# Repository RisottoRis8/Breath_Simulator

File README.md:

# Syringe-Based Breathing Simulator

University biomedical engineering project developed by Gruppo Viola: a motorized syringe generates controlled air flow at its outlet. The system combines a BLDC motor with an ESCON 50/5 drive, encoder feedback, Sensirion pressure or mass-flow sensing, PID control, BLE communication and a desktop monitoring GUI.

This repository presents the final ESP32-based system together with its electronics, control software, measurement data and technical documentation. Earlier firmware, interface and hardware iterations are preserved separately as supporting development history.

## System overview

The final firmware runs on an ESP32 and coordinates:

- flow sensing through SDP810 or SFM3300 devices;
- motor control through the ESCON driver;
- incremental encoder feedback and homing signals;
- PID regulation of the generated flow;
- external SPI EEPROM storage;
- HM-10 compatible BLE telemetry and commands.

The final architecture is supported by a custom control board and a desktop BLE interface. Earlier STM32 and ESP32 bridge implementations are preserved as development iterations.

## Repository map

| Area | Contents |
| --- | --- |
| [docs](docs/) | Report, architecture notes, protocol notes and project catalog |
| [firmware](firmware/) | ESP32 and STM32 firmware area |
| [software/gui](software/gui/) | Main desktop control interface, [main_gui.py](software/gui/main_gui.py) |
| [software/tools](software/tools/) | BLE terminal, CSV visualizer and Python dependency notes |
| [hardware](hardware/) | KiCad boards, custom libraries and board documentation |
| [analysis/matlab](analysis/matlab/) | Measurement interpolation and resistance-analysis scripts |
| [data/measurements/raw](data/measurements/raw/) | Original experimental CSV measurements |
| [mechanical/renders](mechanical/renders/) | Syringe assembly render |
| [archive](archive/) | GUI prototypes and duplicate/legacy experiments |
| [docs/references/datasheets](docs/references/datasheets/) | Component reference documents |
| [archive/sensor-sdp800](archive/sensor-sdp800/) | Sensor sample-code project and documentation |

The detailed working inventory is in [docs/PROJECT_CATALOG.md](docs/PROJECT_CATALOG.md).

## Final system

- **Controller:** [firmware/esp32/main](firmware/esp32/main) coordinates sensing, encoder feedback, motor actuation, PID flow regulation, EEPROM storage and BLE communication.
- **Control interface:** [software/gui/main_gui.py](software/gui/main_gui.py) provides BLE discovery, connection management, real-time flow/position/PWM plots, operating modes, calibration controls, logging and emergency stop.
- **Electronics:** [hardware/motherboard-r2](hardware/motherboard-r2) and [hardware/pogo-adapter](hardware/pogo-adapter) contain the KiCad designs for the control board and sensor adapter. The original motherboard design is preserved as [motherboard-r1](hardware/motherboard-r1).
- **Validation data:** [data/measurements/raw](data/measurements/raw/) contains the experimental acquisitions used during characterization and analysis.

## Communication status

The final ESP32 interface uses an HM-10-compatible BLE service (`FFE0/FFE1`) and telemetry frames in the form `SNSR <flow> <encoder_position> <pwm>`. The communication details are summarized in [docs/protocol.md](docs/protocol.md).

The earlier Nordic UART bridge and STM32 variants remain available in [archive](archive/) as development iterations and are not part of the primary ESP32 control path.

## Running the Python tools

The main GUI requires Python packages including PyQt6, pyqtgraph, bleak and qasync. The BLE terminal declares its dependency in [requirements-ble.txt](software/tools/requirements-ble.txt).

The CSV visualizer is a separate Streamlit utility:

```text
streamlit run software/tools/visualizer.py
```

Its expected columns are `Timestamp_s` and `Pressione_Pa`; the raw measurements commonly use `Time_s` and `Pressure_Pa`, so they are not directly interchangeable yet.

## Firmware and hardware

The Arduino ESP32 sketch is located in [firmware/esp32/main](firmware/esp32/main) and uses the local NimBLE-Arduino library in [firmware/esp32/libraries](firmware/esp32/libraries).

KiCad source files are separated from local state, backups and manufacturing exports. The root [.gitignore](.gitignore) excludes regenerable artifacts while keeping source schematics, PCB files, custom libraries and experimental measurements available for review.

## Project documentation

- [Project catalog](docs/PROJECT_CATALOG.md)
- [Communication protocol notes](docs/protocol.md)
- [Project report](docs/report_biomed.pdf)
- [Code-flow diagram](docs/architecture/code-flow-diagram.drawio)
- [Firmware pseudocode](docs/architecture/codice.pseudo)
- [Assembly render](mechanical/renders/syringe-assembly.jpg)

## Development history

Previous ESP32 sketches, STM32 firmware, BLE bridges and GUI prototypes are preserved in [archive](archive/). They document the iterations that led to the final ESP32 architecture, while the project entrypoints above describe the system delivered by the team.

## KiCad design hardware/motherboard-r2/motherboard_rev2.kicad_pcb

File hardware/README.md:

# Hardware

KiCad source projects, custom libraries and board revisions will be grouped here. Generated manufacturing output and local KiCad state are excluded by the root `.gitignore`.

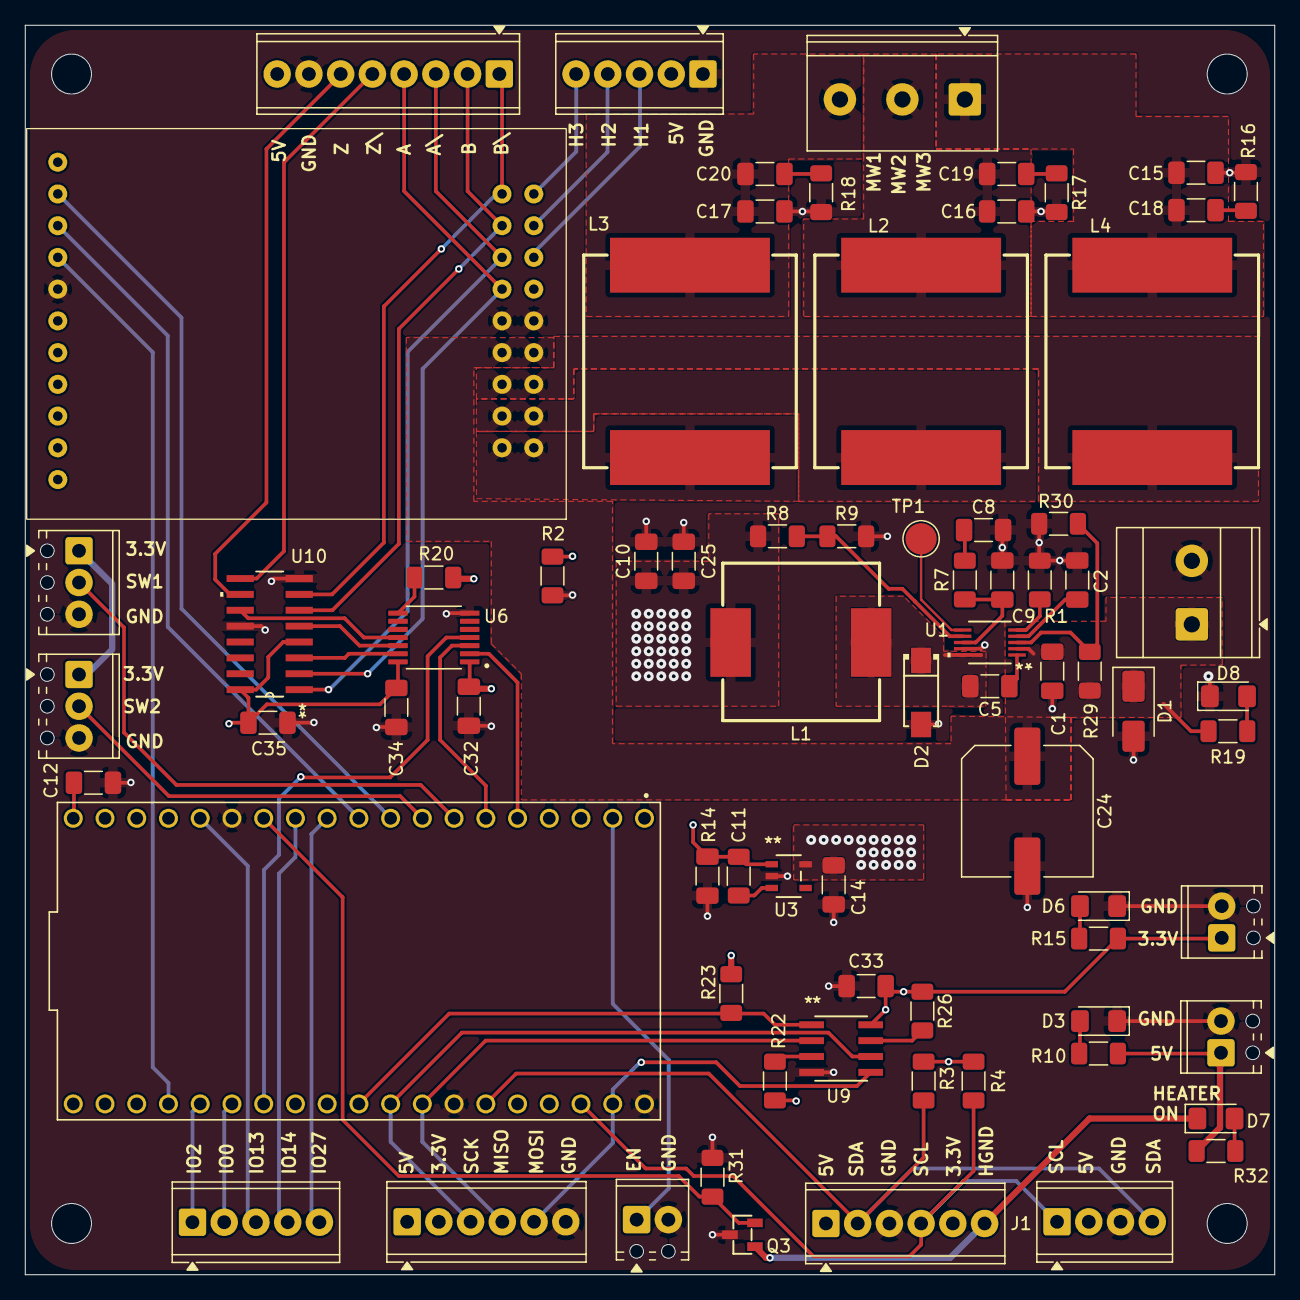
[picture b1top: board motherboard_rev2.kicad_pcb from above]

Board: 4 copper layers, 100.0 x 100.0 mm, 79 parts (0 on the bottom side), 64 nets.

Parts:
C1: 4u7; C_1206_3216Metric_Pad1.33x1.80mm_HandSolder
C2: 6n8; C_1206_3216Metric_Pad1.33x1.80mm_HandSolder
C5, C32, C33, C34, C35: 100n; C_1206_3216Metric_Pad1.33x1.80mm_HandSolder
C8: 1n8; C_1206_3216Metric_Pad1.33x1.80mm_HandSolder
C9: 1p2; C_1206_3216Metric_Pad1.33x1.80mm_HandSolder
C10, C25: 47u; C_1206_3216Metric_Pad1.33x1.80mm_HandSolder
C11, C12, C14: 1u; C_1206_3216Metric_Pad1.33x1.80mm_HandSolder
C15, C16, C17: 150p; C_1206_3216Metric_Pad1.33x1.80mm_HandSolder
C18, C19, C20: 330p; C_1206_3216Metric_Pad1.33x1.80mm_HandSolder
C24: 220u; C_Elec_10x10.2
D1: SMAJ26A; D_SMA
D2: SS24FL; SMA_L4.4-W2.8-LS5.4-RD
D3: LED_ORANGE; LED_1206_3216Metric_Pad1.42x1.75mm_HandSolder
D6: LED_BLUE; LED_1206_3216Metric_Pad1.42x1.75mm_HandSolder
D7: LED_YELLOW; LED_1206_3216Metric_Pad1.42x1.75mm_HandSolder
D8: LED_GREEN; LED_1206_3216Metric_Pad1.42x1.75mm_HandSolder
E1: escon; escon_vero
H1, H2, H3, H4: MountingHole; MountingHole_3.2mm_M3
J1: Conn_01x04; TerminalBlock_Phoenix_MPT-0,5-4-2.54_1x04_P2.54mm_Horizontal
J2, J8: Conn_01x06; TerminalBlock_Phoenix_MPT-0,5-6-2.54_1x06_P2.54mm_Horizontal
J3: Conn_01x08; TerminalBlock_Phoenix_MPT-0,5-8-2.54_1x08_P2.54mm_Horizontal
J5, J6: Conn_01x03; TerminalBlock_Phoenix_MPT-0,5-3-2.54_1x03_P2.54mm_Horizontal
J7, J11: Conn_01x05; TerminalBlock_Phoenix_MPT-0,5-5-2.54_1x05_P2.54mm_Horizontal
J9: Conn_01x02; TerminalBlock_Phoenix_MKDS-3-2-5.08_1x02_P5.08mm_Horizontal
J10: Screw_Terminal_01x03; TerminalBlock_Phoenix_PT-1,5-3-5.0-H_1x03_P5.00mm_Horizontal
J13, J14, J16: Conn_01x02; TerminalBlock_Phoenix_MPT-0,5-2-2.54_1x02_P2.54mm_Horizontal
L1: 47u; IND-SMD_L13.5-W12.6_125CDMCC-DS
L2, L3, L4: 22uH; IND-SMD_L17.0-W17.0_YSPIA1770-100M
Q3: NMOS; SOT-23-3_L2.9-W1.3-P1.90-LS2.4-BR
R1: 249k; R_1206_3216Metric_Pad1.30x1.75mm_HandSolder
R2: 390 ohm; R_1206_3216Metric_Pad1.30x1.75mm_HandSolder
R3, R4: 4.7K; R_1206_3216Metric_Pad1.30x1.75mm_HandSolder
R7: 133k; R_1206_3216Metric_Pad1.30x1.75mm_HandSolder
R8: 52k3; R_1206_3216Metric_Pad1.30x1.75mm_HandSolder
R9, R10, R14, R15, R19, R20, R31: 10k; R_1206_3216Metric_Pad1.30x1.75mm_HandSolder
R16, R17, R18: 390; R_1206_3216Metric_Pad1.30x1.75mm_HandSolder
R22, R23, R26: 10K; R_1206_3216Metric_Pad1.30x1.75mm_HandSolder
R29: 105k; R_1206_3216Metric_Pad1.30x1.75mm_HandSolder
R30: 6k49; R_1206_3216Metric_Pad1.30x1.75mm_HandSolder
R32: 1k; R_1206_3216Metric_Pad1.30x1.75mm_HandSolder
TP1: TestPoint; TestPoint_Pad_D2.5mm
U1: TPS54140ADGQR; DGQ10_1P88X1P57_TEX
U2: NODEMCU-32S; MODULE_NODEMCU-32S
U3: AP2112K-3.3TRG1; SOT_RG1_DIO
U6: TXS0104EPWR; SOP65P640X120-14N
U9: 25LC256-I/SN; SOIC8-N_MC_MCH
U10: AM26LS32ACDR; D16

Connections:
+3.3V: C14.1, C32.1, C33.1, J2.5, J5.1, J6.1, J8.2, J14.1, R3.1, R4.1, R15.1, R20.1, R22.1, R23.1, R26.1, U3.5 (VOUT), U6.1 (VCCA), U9.8 (VCC)
+5V: C10.1, C11.1, C12.1, C25.1, C34.1, C35.1, E1.11 (+5_VDC), J1.2, J2.1, J3.8, J8.1, J11.2, J13.1, L1.2, R2.1, R8.1, R10.1, R14.2, R32.1, U2.J1_19 (5V), U3.1 (VIN), U6.14 (VCCB), U10.4 (G), U10.16 (VCC)
+24V: C1.1, C24.1, D1.1 (A1), E1.7 (Vcc), E1.8 (Vcc), J9.1, R19.1, R29.1, U1.2 (VIN)
/CONNECTORS/ENABLE: J16.1, U2.J1_2 (EN)
/CONNECTORS/ENC_A: E1.12 (ENC_CH_A), J3.4, U10.2 (1A)
/CONNECTORS/ENC_A\: E1.14 (ENC_CH_A\), J3.3, U10.1 (1B)
/CONNECTORS/ENC_B: E1.16 (ENC_CH_B), J3.2, U10.6 (2A)
/CONNECTORS/ENC_B\: E1.18 (ENC_CH_B\), J3.1, U10.7 (2B)
/CONNECTORS/ENC_Z: J3.6, U10.10 (3A)
/CONNECTORS/ENC_Z\: J3.5, U10.9 (3B)
/CONNECTORS/H1: E1.13 (H1), J11.3
/CONNECTORS/H2: E1.15 (H2), J11.4
/CONNECTORS/H3: E1.17 (H3), J11.5
/CONNECTORS/HEAT_GND: D7.1 (K), J2.6, Q3.1 (D)
/CONNECTORS/IO0: J7.2, U2.J2_14 (IO0)
/CONNECTORS/IO2: J7.1, U2.J2_15 (IO2)
/CONNECTORS/IO13: J7.3, U2.J1_15 (IO13)
/CONNECTORS/IO14: J7.4, U2.J1_12 (IO14)
/CONNECTORS/IO27: J7.5, U2.J1_11 (IO27)
/CONNECTORS/MW1_motor: C17.1, C20.1, J10.3, L3.2
/CONNECTORS/MW2_motor: C16.1, C19.1, J10.2, L2.2
/CONNECTORS/MW3_motor: C15.1, C18.1, J10.1, L4.2
/CONNECTORS/SCL: J1.1, J2.4, R4.2, U2.J2_3 (IO22)
/CONNECTORS/SDA: J1.4, J2.2, R3.2, U2.J2_6 (IO21)
/CONNECTORS/SPI_MISO: J8.4, U2.J2_8 (IO19), U9.2 (SO)
/CONNECTORS/SPI_MOSI: J8.5, U2.J2_2 (IO23), U9.5 (SI)
/CONNECTORS/SPI_SCK: J8.3, U2.J2_9 (IO18), U9.6 (SCK)
/CONNECTORS/SW_1: J5.2, U2.J1_7 (IO32)
/CONNECTORS/SW_2: J6.2, U2.J1_8 (IO33)
/ESCON 50_5/D_IN_1: E1.22 (Dig_IN_1), U2.J2_16 (IO15)
/ESCON 50_5/D_IN_2: E1.21 (Dig_IN_2), U2.J1_10 (IO26)
/ESCON 50_5/D_IO_3: E1.20 (Dig_InOut_3), U2.J1_9 (IO25)
/ESCON 50_5/MW1: E1.1 (motor_winding_1), E1.2 (motor_winding_1), L3.1
/ESCON 50_5/MW2: E1.3 (motor_winding_2), E1.4 (motor_winding_2), L2.1
/ESCON 50_5/MW3: E1.5 (motor_winding_3), E1.6 (motor_winding_3), L4.1
/ESP32/EEPROM_CS: R23.2, U2.J2_10 (IO5), U9.1 (*CS)
/ESP32/ENC_A: U2.J1_5 (IO34), U6.2 (A1)
/ESP32/ENC_B: U2.J1_6 (IO35), U6.3 (A2)
/ESP32/ENC_Z: U2.J2_13 (IO4), U6.4 (A3)
/ESP32/HEATER: Q3.2 (G), R31.1, U2.J1_13 (IO12)
/level_shifter/ENC_A_UNSHIFT: U6.13 (B1), U10.3 (1Y)
/level_shifter/ENC_B_UNSHIFT: U6.12 (B2), U10.5 (2Y)
/level_shifter/ENC_Z_UNSHIFT: U6.11 (B3), U10.11 (3Y)
GND: C1.2, C2.2, C8.2, C9.2, C10.2, C11.2, C12.2, C14.2, C15.2, C16.2, C17.2, C24.2, C25.2, C32.2, C33.2, C34.2, C35.2, D1.2 (A2), D2.2 (A), D3.1 (K), D6.1 (K), D8.1 (K), E1.9 (GND), E1.10 (GND), E1.23 (GND), J1.3, J2.3, J3.7, J5.3, J6.3, J8.6, J9.2, J11.1, J13.2, J14.2, J16.2, Q3.3 (S), R1.2, R2.2, R9.2, R16.2, R17.2, R18.2, R30.2, R31.2, U1.9 (GND), U2.J1_14 (GND), U2.J2_1 (GND), U2.J2_7 (GND), U3.2 (GND), U6.7 (GND), U9.4 (VSS), U10.8 (GND), U10.12 (*G)
unnamed: C8.1, R7.2
unnamed: C18.2, R16.1
unnamed: C19.2, R17.1
unnamed: C20.2, R18.1
unnamed: C5.2, D2.1 (K), L1.1, U1.10 (PH)
unnamed: D3.2 (A), R10.2
unnamed: D6.2 (A), R15.2
unnamed: D7.2 (A), R32.2
unnamed: D8.2 (A), R19.2
unnamed: C5.1, U1.1 (BOOT)
unnamed: C9.1, R7.1, U1.8 (COMP)
unnamed: R29.2, R30.1, U1.3 (EN)
unnamed: TP1.1 (1_1), U1.6 (PWRGD)
unnamed: R1.1, U1.5 (RT/CLK)
unnamed: C2.1, U1.4 (SS/TR)
unnamed: R8.2, R9.1, U1.7 (VSENSE)
unnamed: R14.1, U3.3 (EN)
unnamed: R20.2, U6.8 (OE)
unnamed: R26.2, U9.7 (*HOLD)
unnamed: R22.2, U9.3 (*WP)

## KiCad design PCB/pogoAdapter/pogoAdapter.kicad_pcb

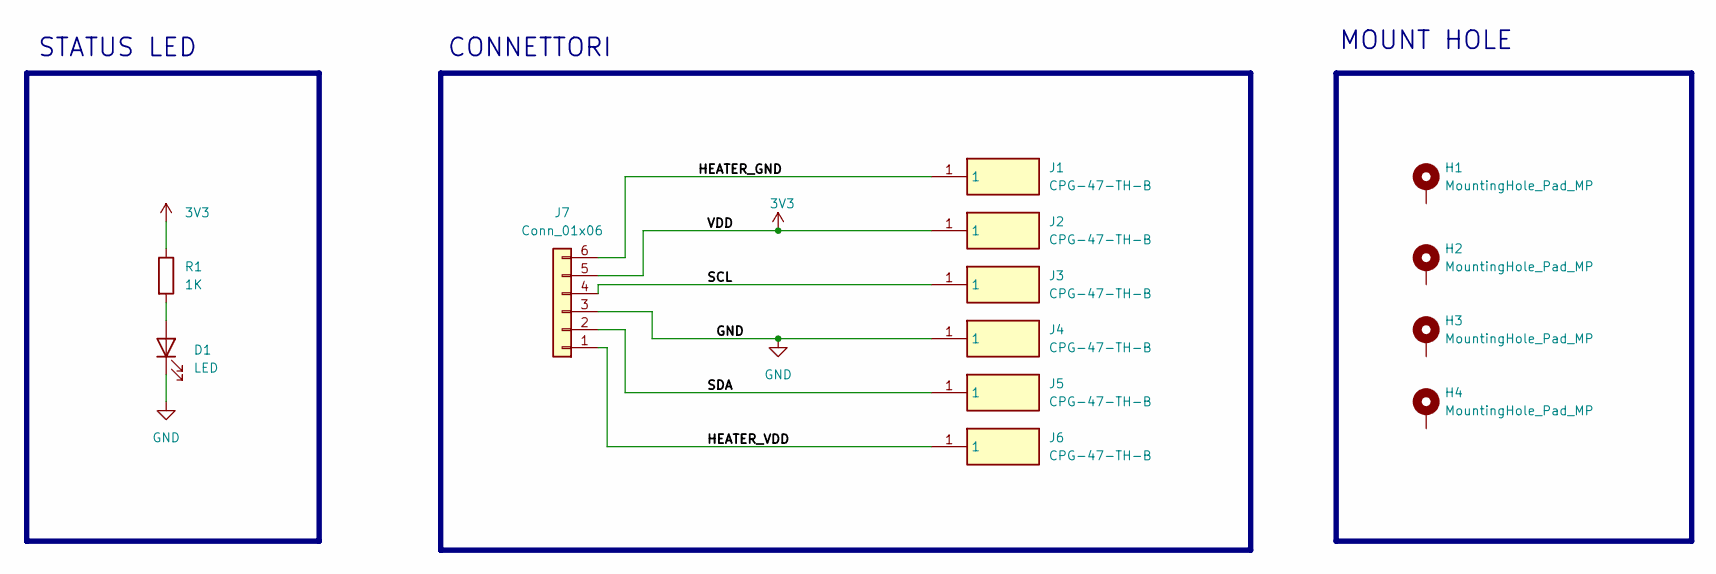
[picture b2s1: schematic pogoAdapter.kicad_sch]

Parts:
D1: LED; LED_1206_3216Metric_Pad1.42x1.75mm_HandSolder
H1, H2, H3, H4: MountingHole_Pad_MP; mountHole_1.8mm
J1, J2, J3, J4, J5, J6: CPG-47-TH-B; CPG47THB; Manufacturer_Part_Number CPG-47-TH-B
J7: Conn_01x06; TerminalBlock_Phoenix_MPT-0,5-6-2.54_1x06_P2.54mm_Horizontal
R1: 1K; R_1206_3216Metric_Pad1.30x1.75mm_HandSolder

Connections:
3V3: J2.1 (1_1), J7.5, R1.1
/HEATER_GND: J1.1 (1_1), J7.6
/HEATER_VDD: J6.1 (1_1), J7.1
/SCL: J3.1 (1_1), J7.4
/SDA: J5.1 (1_1), J7.2
GND: D1.1 (K), H1.1, H2.1, H3.1, H4.1, J4.1 (1_1), J7.3
unnamed: D1.2 (A), R1.2

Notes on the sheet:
MOUNT HOLE
CONNETTORI
STATUS LED

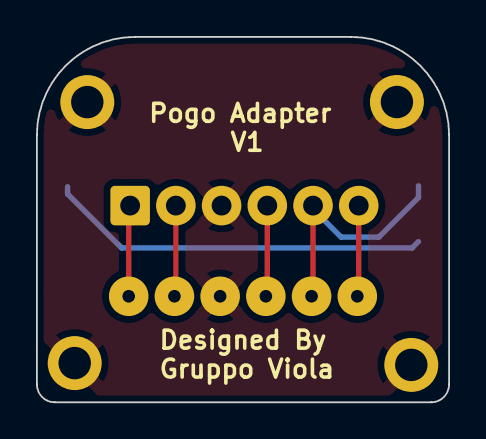
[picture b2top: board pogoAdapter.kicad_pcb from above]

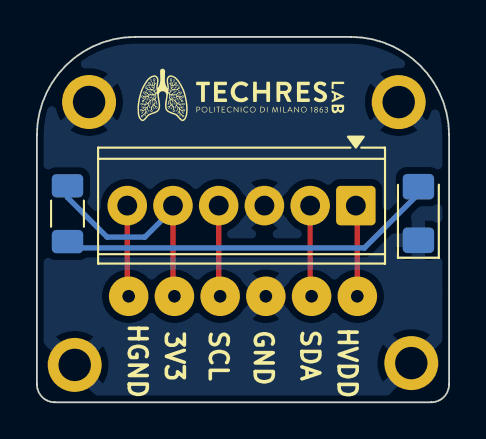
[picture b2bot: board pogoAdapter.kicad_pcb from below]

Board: 2 copper layers, 22.9 x 20.3 mm, 13 parts (3 on the bottom side), 7 nets.

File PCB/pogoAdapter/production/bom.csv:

Designator,Footprint,Quantity,Value,LCSC Part #
D1,1206,1,LED,
"J1, J2, J3, J4, J5, J6",CPG47THB,6,CPG-47-TH-B,
J7,"TerminalBlock_Phoenix_MPT-0,5-6-2.54_1x06_P2.54mm_Horizontal",1,Conn_01x06,
R1,1206,1,1K,

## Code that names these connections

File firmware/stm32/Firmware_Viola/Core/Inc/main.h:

/* USER CODE BEGIN Header */
/**
  ******************************************************************************
  * @file           : main.h
  * @brief          : Header for main.c file.
  *                   This file contains the common defines of the application.
  ******************************************************************************
  * @attention
  *
  * Copyright (c) 2026 STMicroelectronics.
  * All rights reserved.
  *
  * This software is licensed under terms that can be found in the LICENSE file
  * in the root directory of this software component.
  * If no LICENSE file comes with this software, it is provided AS-IS.
  *
  ******************************************************************************
  */
/* USER CODE END Header */

/* Define to prevent recursive inclusion -------------------------------------*/
#ifndef __MAIN_H
#define __MAIN_H

#ifdef __cplusplus
extern "C" {
#endif

/* Includes ------------------------------------------------------------------*/
#include "stm32l4xx_hal.h"

/* Private includes ----------------------------------------------------------*/
/* USER CODE BEGIN Includes */

/* USER CODE END Includes */

/* Exported types ------------------------------------------------------------*/
/* USER CODE BEGIN ET */

/* USER CODE END ET */

/* Exported constants --------------------------------------------------------*/
/* USER CODE BEGIN EC */

/* USER CODE END EC */

/* Exported macro ------------------------------------------------------------*/
/* USER CODE BEGIN EM */

/* USER CODE END EM */

/* Exported functions prototypes ---------------------------------------------*/
void Error_Handler(void);

/* USER CODE BEGIN EFP */

/* USER CODE END EFP */

/* Private defines -----------------------------------------------------------*/
#define FAULT_ESCON_Pin GPIO_PIN_14
#define FAULT_ESCON_GPIO_Port GPIOC
#define ENC_A_Pin GPIO_PIN_0
#define ENC_A_GPIO_Port GPIOA
#define ENC_B_Pin GPIO_PIN_1
#define ENC_B_GPIO_Port GPIOA
#define EN_ESCON_Pin GPIO_PIN_0
#define EN_ESCON_GPIO_Port GPIOB
#define DIR_ESCON_Pin GPIO_PIN_1
#define DIR_ESCON_GPIO_Port GPIOB
#define PWM_ESCON_Pin GPIO_PIN_8
#define PWM_ESCON_GPIO_Port GPIOA
#define HC_05_TX_Pin GPIO_PIN_9
#define HC_05_TX_GPIO_Port GPIOA
#define HC_05_RX_Pin GPIO_PIN_10
#define HC_05_RX_GPIO_Port GPIOA
#define ENC_Z_Pin GPIO_PIN_12
#define ENC_Z_GPIO_Port GPIOA
#define LED_GREEN_Pin GPIO_PIN_5
#define LED_GREEN_GPIO_Port GPIOA
#define SPI_SCK_Pin GPIO_PIN_3
#define SPI_SCK_GPIO_Port GPIOB
#define SPI_MISO_Pin GPIO_PIN_4
#define SPI_MISO_GPIO_Port GPIOB
#define SPI_MOSI_Pin GPIO_PIN_5
#define SPI_MOSI_GPIO_Port GPIOB
#define SCL_Pin GPIO_PIN_6
#define SCL_GPIO_Port GPIOB
#define SDA_Pin GPIO_PIN_7
#define SDA_GPIO_Port GPIOB

/* USER CODE BEGIN Private defines */

/* USER CODE END Private defines */

#ifdef __cplusplus
}
#endif

#endif /* __MAIN_H */

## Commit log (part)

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2026-04-01 Guidelines nel readme
2026-04-01 Datasheets
2026-04-01 added 3D and PCB folders,created default pcb project on kicad
2026-04-01 added placeholder on 3d folder
2026-04-01 schematic template added
2026-04-02 Aggiornato ReadMe con RoadMap implementazione
2026-04-02 Added Project Blueprint
2026-04-04 Varie modifiche
2026-04-04 Pseudocode
2026-04-07 datasheet flussimetro
2026-04-08 added kicad libraries for power
2026-04-08 started power schematic of pcb
2026-04-08 datasheet corretto
2026-04-10 updated sch power
2026-04-15 aggiunto driver escon in libreria e nel progetto schematico
2026-04-15 test kicad collab
2026-04-15 layout connettori + note
2026-04-15 added hierrcical labels mcu, added filters for escon + labels
2026-04-15 match label
2026-04-15 More code
2026-04-15 reverse current protection on ESCON+others
2026-04-17 collegamenti tra blocchi schematico, sistemati connettori,finita la parte di shunt monitor per back EMF escon, aggiunti status LED, aggiunti bulk cap su alimentazione+altre modifiche
2026-04-22 schematics need only sizing
2026-04-22 sizing schematics done
2026-04-22 assegnazione footprint connettori
2026-04-22 aggiunta footprint escon
2026-04-22 added footprint for all components
2026-04-22 added last footprint on sch
2026-04-24 pcb layout
2026-04-25 Software crap
2026-04-25 pcb layout : collegamento piste + vie + cambio connettori
2026-04-29 resolved pcb errors from drc, generated test output files
2026-05-03 Finito Calibratore
2026-05-06 salvo modifiche
2026-05-06 ignore DS_Store
2026-05-07 Misure!
2026-05-30 Ignore macOS DS_Store files
2026-05-30 Remove DS_Store from repository
2026-06-19 cacaminchia
